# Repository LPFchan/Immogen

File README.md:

# Immogen — Ninebot G30 BLE Immobilizer

**Immogen** is a three-part BLE immobilizer system for the Ninebot Max G30, consisting of **[Uguisu](https://github.com/LPFchan/Immogen/tree/main/Uguisu#readme)** (key fob), **[Guillemot](https://github.com/LPFchan/Immogen/tree/main/Guillemot#readme)** (deck receiver), and **[Whimbrel](https://github.com/LPFchan/Whimbrel)** (Web Serial provisioning app).

Guillemot sits inline between the battery and ESC via an XT60 splice. Without a valid BLE unlock from Uguisu, the scooter stays inoperable. Male/female pigtails keep the install reversible—no permanent modification required.

```
┌─────────────────┐       BLE advertisement        ┌──────────────────────┐
│  UGUISU (FOB)   │ ─────────────────────────────> │ GUILLEMOT (RECEIVER) │
│  XIAO nRF52840  │       (2.4 GHz, ~2 m)          │  XIAO nRF52840       │
└───────┬─────────┘                                └──────────┬───────────┘
        │                                                     │
        │                 ┌────────────────────┐              │
        └──────(USB-C)──> │ WHIMBREL (WEB APP) │ <──(USB-C)───┘
       (Provisioning)     │ Chrome / Edge      │    (Provisioning)
                          └────────────────────┘
```

## Repository Structure

| Path             | Description                                                                                                                                                                       |
| ---------------- | --------------------------------------------------------------------------------------------------------------------------------------------------------------------------------- |
| `Uguisu/`    | Key fob — firmware, KiCad, BOM. Button press → 2 s BLE broadcast → sleep. [README](https://github.com/LPFchan/Immogen/tree/main/Uguisu#readme)                                 |
| `Guillemot/` | Deck receiver — firmware, KiCad, BOM. Duty-cycled scan (5%), validates adverts → SR latch → power gate. [README](https://github.com/LPFchan/Immogen/tree/main/Guillemot#readme) |
| `lib/`       | Shared C++ library: AES-128-CCM MIC, provisioning loop, LittleFS counter storage                                                                                                  |
| `tools/`     | LED visualizer, BLE timing simulator, buzzer tuner (HTML); MIC test vectors (`gen_mic.py`)                                                                                        |
| `logs/`      | Migration reports and guides                                                                                                                                                      |

## BLE Protocol

Advertisement-only; no persistent connection. Both devices share a company ID and pre-shared key (PSK). Each advertisement carries a 13-byte payload after the 2-byte company ID:

| Offset | Size | Field   | Purpose                    |
| ------ | ---- | ------- | -------------------------- |
| 0      | 4    | counter | Anti-replay, monotonic     |
| 4      | 1    | command | 0x01 = Unlock, 0x02 = Lock |
| 5      | 8    | mic     | AES-128-CCM auth tag       |

For full protocol details see the [Guillemot](https://github.com/LPFchan/Immogen/tree/main/Guillemot#readme) and [Uguisu](https://github.com/LPFchan/Immogen/tree/main/Uguisu#readme) READMEs.

## Quick Start

Pre-built firmware is available on the [Releases](https://github.com/LPFchan/Immogen/releases) page. Use [Whimbrel](https://github.com/LPFchan/Whimbrel) to flash and provision keys via Web Serial.

**Build from source:**

```bash
# Deck receiver
cd Guillemot/firmware && pio run

# Key fob
cd Uguisu/firmware && pio run
```

## Roadmap

- Uguisu enclosure CAD (3D print).
- First-build validation: PPK2 power, BLE range through deck, pre-charge waveform.

## Safety & Legal

- Prototype security/power-interrupt device. Use at your own risk.
- Not affiliated with Segway-Ninebot.
- **Do not test lock behavior while riding.**

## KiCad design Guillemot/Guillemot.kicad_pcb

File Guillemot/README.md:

# Guillemot — Ninebot G30 BLE Immobilizer Receiver

Guillemot is the deck receiver in a three-part immobilizer system ([Uguisu](https://github.com/LPFchan/Immogen/tree/main/Uguisu) fob + [Whimbrel](https://github.com/LPFchan/Whimbrel) web app) for the Ninebot Max G30. It validates encrypted BLE advertisements from the fob and controls an SR latch that gates battery-to-ESC power via an inline XT60 splice. Male/female pigtails make it fully reversible—no permanent modification to the vehicle. Protocol and cryptography are handled by the shared [lib/](https://github.com/LPFchan/Immogen/tree/main/lib) in this monorepo ([Immogen](https://github.com/LPFchan/Immogen)).

---

## Hardware

### Placement

Mount Guillemot on the plastic underside of the deck for good 2.4 GHz RF.

### Components & BOM (~$20)

| Ref       | Part            | Notes                                                             | JLCPCB #         | Cost   |
| --------- | --------------- | ----------------------------------------------------------------- | ---------------- | ------ |
| U1        | XIAO nRF52840   | MCU: BLE scanning, latch control, buzzer PWM                      | Seeed            | $8.23  |
| U2        | SN74LVC2G02DCTR | SR latch: Q = unlock. 10 nF + 100 kΩ differentiator for POR pulse | C94600 (ext.)    | $0.53  |
| PS1       | TPSM365R6V3RDNR | Buck: 3–65 V in, 3.3 V/600 mA, 4 μA Iq. Feeds XIAO 3V3 directly.  | C18208843 (ext.) | $3.59  |
| Q1        | IPB042N10N3G    | Main MOSFET: 100 V/137 A, D2PAK, low-side GND return              | C69300 (ext.)    | $0.75  |
| Q2        | AO3422          | Pre-charge FET, inrush ~0.8 A. Driven by latch Q.                 | C37130 (ext.)    | $0.23  |
| Q3        | SI2309CDS       | Bleeder P-FET: disconnects 10 kΩ bleeder when locked (0 μA)       | C10493 (ext.)    | $0.23  |
| Q4        | 2N7002          | Gate drive                                                        | C8545            | $0.01  |
| Q5, Q6    | MMBT3904        | Buzzer driver                                                     | C20526           | $0.02  |
| BZ1       | FUET-1230       | Buzzer: 12×12×3 mm SMD, 4 kHz. Driven by MMBT3904                 | C391037 (ext.)   | $0.47  |
| D1        | BZT52C12-7-F    | 12 V Zener                                                        | C124196 (ext.)   | $0.11  |
| D2        | BZT52C10-7-F    | 10 V Zener                                                        | C155227 (ext.)   | $0.10  |
| D3, D4    | 1N4148W         | Gate isolation from buzzer rail sag                               | C81598           | $0.01  |
| D5        | SMBJ45A         | 45 V TVS diode for transient suppression                          | C114005 (ext.)   | $0.08  |
| C1        | 10 nF (0603)    | POR pulse differentiator                                          | C57112           | $0.003 |
| C2        | 100 µF (1210)   | Bulk decoupling. EMK325ABJ107MM-P 16V X5R ±20%                   | C90143 (ext.)    | $0.31  |
| C3, C4    | 1 µF (0603)     | RC delay bypass, gate isolation                                   | C15849           | $0.01  |
| R1, R2    | 100 kΩ (0603)   | Latch input pull-downs (prevent floating during WDT reset)        | C25803           | $0.006 |
| R3, R7    | 100 kΩ (0603)   | Gate drive, RC delay (τ = 100 ms)                                 | C25803           | $0.006 |
| R4        | 1 MΩ (0603)     | P-FET gate pull-up                                                | C22935           | $0.001 |
| R5        | 10 kΩ (0603)    | Bleeder resistor                                                  | C25804           | $0.001 |
| R6        | 4.7 kΩ (0603)   | Piezo buzzer discharge resistor                                   | C23162           | $0.001 |
| R8        | 47 Ω 2 W (2512) | Pre-charge resistor, inrush ~0.77–0.89 A                         | C136992 (ext.)   | $0.10  |
| TP1–5     | XT60 + 12 AWG   | Pigtails and GND jumper                                           | Generic          | —      |
| —         | PCB             | 54×34 mm, 2 oz outer                                              | JLCPCB           | $1.60  |

JLCPCB P&P for SMT. Hand-solder XIAO edges, XT60 pigtails, and the GND jumper.

### PCB Layout

4-layer, 54×34 mm, 2 oz outer copper, designed for 30 A continuous.

- **12 AWG GND jumper (critical):** Main battery return bypasses inner layers. Run an external silicone wire from the `BAT-` XT60 pad to the MOSFET source pad.
- **Power traces:** `+BATT` and `ESC-` as top-layer pours. No high-current vias.
- **Clearance:** ≥ 0.6 mm between 42 V power and 3.3 V logic.
- **Pre-charge trace:** Q2 → R8 → `ESC-` routed at **1.0 mm** to survive initial ~40 W inrush surge.
- **RF keepout:** Strip copper on all layers under the XIAO's BLE antenna trace.
- **Assembly:** Single-sided (F.Cu) SMT for easy JLCPCB PCBA.

### Operation

- **Unlock flow:** Uguisu advert → MCU validates → SET latch → Q HIGH → pre-charge 100 ms → MOSFET ON → buzzer tone.
- **Lock flow:** Uguisu advert → MCU validates → buzzer tone → RESET latch → Q LOW → P-FET OFF, pre-charge OFF → MOSFET OFF.
- **Power (locked):** ~306 μA (buck Iq + 5% duty-cycled scan + latch). At 306 μA, a G30 (15.3 Ah) would theoretically take ~5.7 years to drain; battery self-discharge (~12 months) dominates in practice. See `logs/15-BLE_POWER_ANALYSIS_AND_DOCUMENTATION_DISCREPANCY.md` for derivation.
- **Buzzer timing:** Unlock tone ~34 ms after 10 V rail up; lock tone before RESET.

### Design Notes

- **EasyEDA → KiCad:** Schematics and PCBs are designed in KiCad. [easyeda2kicad](https://github.com/wokwi/easyeda2kicad) is used to import symbols and footprints from EasyEDA/LCSC. Example: `easyeda2kicad --full --lcsc_id=Cxxxx` (replace `Cxxxx` with the LCSC part number).
- **Latch Input Pull-downs (100 kΩ):** R1 and R2 hold `MCU_D0` (SET) and `MCU_D1` (RESET) strictly LOW. This is critical because the nRF52840's pins float (high-impedance) during the 8-second hardware Watchdog Timer (WDT) reset cycle. Without these resistors, noise or capacitive coupling could randomly toggle the latch and power state while the MCU reboots.
- **AO3422:** 55 V Vds provides margin over the 42 V bus when locked.
- **Gate drive R (100 kΩ):** Protects the 2N7002 and BZT Zeners.
- **POR circuit (10 nF + 100 kΩ):** 1 ms RC differentiator—brief pulse zeros the latch at power-on.
- **RC delay (100 kΩ + 1 μF):** 1N4148W bypass for fast turn-off.
- **Gate isolation (1N4148W + cap):** Buzzer draw exceeds bleeder supply; diode and 1 μF hold cap prevent gate sag during tones (Vgs ≈ 9.3 V).
- **Gate pull-down (MMBT3904):** Via Q̄/RC, discharges hold cap for instant OFF.
- **IPB042N10N3G:** Outperforms TO-220 standing upright in sealed deck enclosures when thermal pad is stitched to B.Cu. **IPB035N10NF2S (3.5 mΩ)** is the long-term successor depending on LCSC stock.

---

## Software

### Firmware

[PlatformIO](https://platformio.org/) project in `firmware/`

Scanning is duty-cycled (25 ms every 500 ms, 5% duty) for reliable detection. P(detect) = 100% per button press because `scanWindow (25 ms) ≥ advInterval (20 ms)` guarantees full phase coverage. The receiver rejects any payload with an invalid AES-CCM MIC or a counter less than or equal to the last seen value (anti-replay). The receiver is also protected against MCU hangs by an 8-second hardware Watchdog Timer (WDT) which triggers a clean reboot without disrupting the latch state.

### Protocol

Validation and crypto via shared [lib/](https://github.com/LPFchan/Immogen/tree/main/lib). See [Immogen README § BLE Protocol](https://github.com/LPFchan/Immogen#ble-protocol) for full specification.

### Onboarding

Use [Whimbrel](https://github.com/LPFchan/Whimbrel) for both tasks:

- **Firmware flashing:** Web-based flasher via Web Serial. Enter bootloader mode with a double-tap on reset.
- **Key provisioning:** Connect via USB; Whimbrel injects the shared AES-128 key. Physical presence is required. The firmware has no serial commands to read the key back.

---

## Safety & Notes

- Prototype security and power-interrupt device. Use at your own risk.
- Do not test lock behavior while riding.
- Not affiliated with Segway-Ninebot.
- Avoid committing KiCad per-user state (`*.kicad_prl`) or lock files.

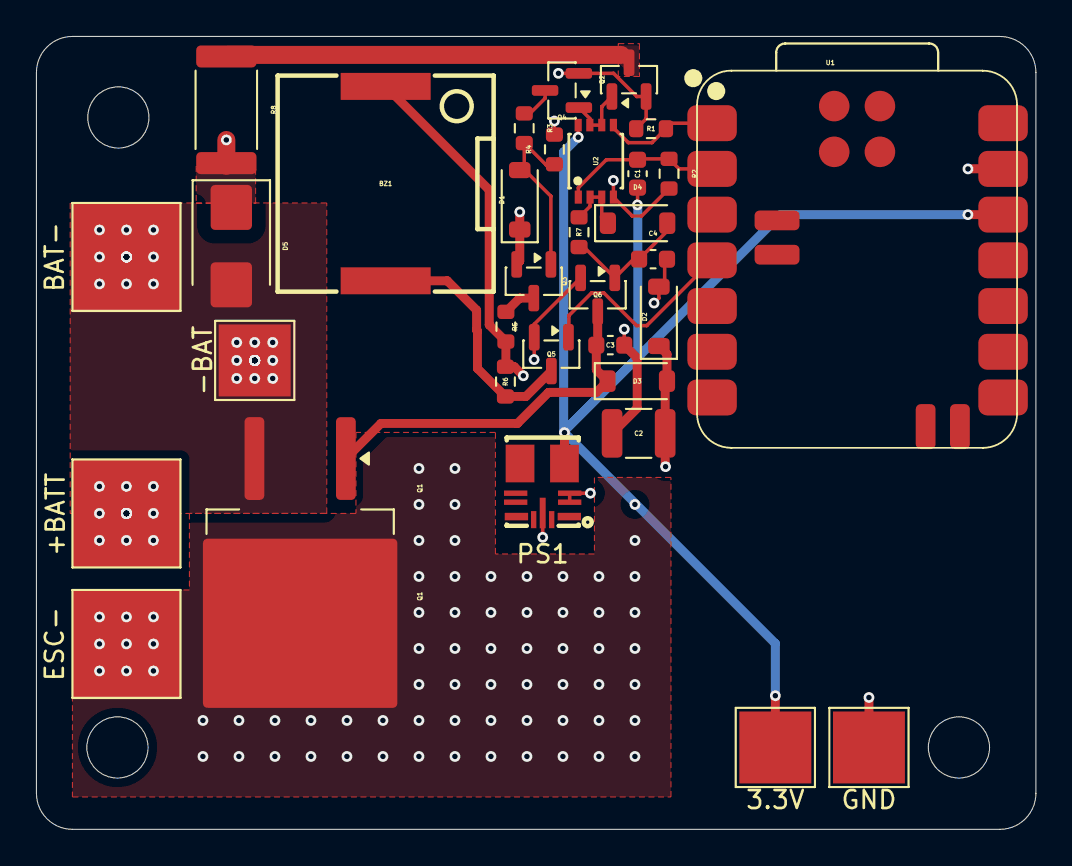
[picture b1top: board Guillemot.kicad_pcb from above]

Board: 4 copper layers, 55.5 x 44.0 mm, 33 parts (0 on the bottom side), 17 nets.

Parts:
3.3V: 3.3V; TestPoint_Pad_4.0x4.0mm
+BATT: ESC+; TestPoint_Pad_6.0x6.0mm
-BAT: WIRE; TestPoint_Pad_4.0x4.0mm
BAT-: BAT-; TestPoint_Pad_6.0x6.0mm
BZ1: FUET-1230; BUZ-SMD_L12.0-W12.0_FUET-1230
C1: 10nF; C_0603_1608Metric
C2: 100µF; C_1210_3225Metric
C3, C4: 1uF; C_0603_1608Metric
D1: BZT52C12-7-F; D_SOD-123
D2: BZT52C10-7-F; D_SOD-123
D3, D4: 1N4148W; D_SOD-123
D5: SMBJ45A; D_SMB
ESC-: ESC-; TestPoint_Pad_6.0x6.0mm
GND: GND; TestPoint_Pad_4.0x4.0mm
PS1: TPSM365R6V3RDNR; QFN-11_L4.5-W3.5-P0.50-TL_TPSM365R6FRDNR
Q1: IPB042N10N3G; TO-263-2
Q2: AO3422; SOT-23
Q3: SI2309CDS; SOT-23
Q4: 2N7002; SOT-23
Q5, Q6: MMBT3904; SOT-23
R1, R2, R3, R7: 100k; R_0603_1608Metric
R4: 1M; R_0603_1608Metric
R5: 10k; R_0603_1608Metric
R6: 4.7k; R_0603_1608Metric
R8: 47 2W; R_2512_6332Metric
U1: XIAO-nRF52840-SMD
U2: SN74LVC2G02DCTR; MSOP-8_L2.9-W2.8-P0.65-LS4.0-BR

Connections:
+BATT: +BATT.1, D1.1 (K), PS1.2 (EN), PS1.3 (VIN), Q3.2 (S), R4.2
/3.3V: 3.3V.1, C1.2, PS1.4 (VOUT), U1.12 (3V3), U2.8 (VCC)
/10V_RAIL: BZ1.1 (+), C2.1, D2.1 (K), D3.2 (A), R5.2, R6.1
/10V_RAW: Q3.3 (D), R5.1
/BUZZER_SINK: BZ1.2, Q5.3 (C), R6.2
/ESC-: D5.1 (A1), ESC-.1, Q1.2 (D), R8.2
/ISO_GATE: C3.1, D3.1 (K), Q1.1 (G), Q6.3 (C)
/MCU_D0: R1.1, U1.1 (P0.02_A0_D0), U2.5 (2A)
/MCU_D1: C1.1, R2.1, U1.2 (P0.03_A1_D1), U2.1 (1A)
/MCU_D3: Q5.1 (B), U1.4 (P0.29_A3_D3)
/NPN_BASE: C4.1, D4.2 (A), Q6.1 (B), R7.2
/PFET_CTRL: Q4.3 (D), R3.1
/PFET_GATE: D1.2 (A), Q3.1 (G), R3.2, R4.1
/PRECHARGE_OUT: Q2.3 (D), R8.1
/QBAR_LOCK: D4.1 (K), R7.1, U2.2 (1B), U2.3 (2Y)
/Q_UNLOCK: Q2.1 (G), Q4.1 (G), U2.6 (2B), U2.7 (1Y)
GND: -BAT.1, BAT-.1, C2.2, C3.2, C4.2, D2.2 (A), D5.2 (A2), GND.1, PS1.10 (GND), Q1.3 (S), Q2.2 (S), Q4.2 (S), Q5.2 (E), Q6.2 (E), R1.2, R2.2, U1.13 (GND), U2.4 (GND)

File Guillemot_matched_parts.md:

# Guillemot BOM - Matched Parts

## Matched Components


| Designator  | Comment         | Footprint                       | Part Name               | LCSC      | Description / Specs                                                                                                                | Qty | Type     | Total Cost |
| ----------- | --------------- | ------------------------------- | ----------------------- | --------- | ---------------------------------------------------------------------------------------------------------------------------------- | --- | -------- | ---------- |
| BZ1         | FUET-1230       | BUZ-SMD_L12.0-W12.0_FUET-1230   | FUET-1230               | C391037   | -20℃~~+70℃ 12mm 12mm 1V~~25V 3.3mm 3V 4kHz 5mA 75dB Passive (Externally Driven) Piezoelectric SMD,12x12mm Buzzers ROHS             | 5   | Extended | $2.3640    |
| C1          | 10nF            | 0603                            | 0603B103K500NT          | C57112    | 10nF 50V X7R ±10% 0603 Multilayer Ceramic Capacitors MLCC - SMD/SMT ROHS                                                           | 5   | Basic    | $0.0140    |
| C2          | 100µF           | 1210                            | CL32A107MPVNNNE         | C23742    | 100uF 10V X5R ±20% 1210 Multilayer Ceramic Capacitors MLCC - SMD/SMT ROHS                                                          | 5   | Extended | $1.5285    |
| C3,C4       | 1uF             | 0603                            | CL10A105KB8NNNC         | C15849    | 1uF 50V X5R ±10% 0603 Multilayer Ceramic Capacitors MLCC - SMD/SMT ROHS                                                            | 5   | Basic    | $0.0720    |
| D1          | BZT52C12-7-F    | D_SOD-123                       | BZT52C12-7-F            | C124196   | -65℃~~+150℃ 100nA@1V 11.4V~~12.7V 12V 150Ω 25Ω 370mW Independent SOD-123 Zener Diodes ROHS                                         | 5   | Extended | $0.5538    |
| D2          | BZT52C10-7-F    | D_SOD-123                       | BZT52C10-7-F            | C155227   | -65℃~~+150℃ 10V 150Ω 200nA 20Ω 370mW 9.4V~~10.6V Independent SOD-123 Zener Diodes ROHS                                             | 5   | Extended | $0.5085    |
| D3,D4       | 1N4148W         | D_SOD-123                       | 1N4148W                 | C81598    | 1.25V@150mA 100V 150mA 1uA@75V 2A 4ns 500mW Independent SOD-123 Switching Diodes ROHS                                              | 10  | Basic    | $0.1100    |
| D5          | SMBJ45A         | D_SMB                           | SMBJ45A                 | C114005   | -65℃~+150℃ 1uA 45V 55.3V 600W@10/1000us 72.7V 8.3A@10/1000us TVS Unidirectional DO-214AA(SMB) ESD and Surge Protection             | 5   | Extended | $0.4221    |
| PS1         | TPSM365R6V3RDNR | CONV_TPSM365R6V3RDNR            | TPSM365R6V3RDNR         | C18208843 | -40℃~~+125℃ 1MHz 2mm 3.3V 3.5mm 3.6V~~65V 4.5mm 4uA 600mA 80.2% Buck Overheat protection、Over Current Protection ±1.5%             | 5   | Extended | $17.9375   |
| Q1          | IPB042N10N3G    | TO-263-2                        | IPB042N10N3G            | C69300    | -55℃~+175℃ 1 N-channel 100V 117nC 137A 214W 3.5V 4.2mΩ@10V 41pF 8.41nF TO-263-3 MOSFETs ROHS                                       | 5   | Extended | $3.7630    |
| Q2          | AO3422          | SOT-23                          | AO3422                  | C37130    | 1 N-channel 10A 12.6pF 160mΩ@4.5V 2V [3.3nC@4.5V](mailto:3.3nC@4.5V) 300pF 55V N-Channel SOT-23 MOSFETs ROHS                       | 5   | Extended | $1.1376    |
| Q3          | SI2309CDS       | SOT-23                          | SI2309CDS-T1-GE3        | C10493    | -55℃~+150℃ 1 P-Channel 1.6A 1.7W 20pF 210pF 28pF 3V [4.1nC@4.5V](mailto:4.1nC@4.5V) 450mΩ@4.5V 60V P-Channel SOT-23-3 MOSFETs ROHS | 5   | Extended | $1.1333    |
| Q4          | 2N7002          | SOT-23                          | 2N7002                  | C8545     | 1 N-channel 115mA 2.5V 225mW 50pF 5pF 5Ω@10V 60V SOT-23 MOSFETs ROHS                                                               | 5   | Basic    | $0.0660    |
| Q5,Q6       | MMBT3904        | SOT-23                          | MMBT3904(RANGE:100-300) | C20526    | -55℃~+150℃ 1 NPN 100 100nA 200mA 200mW 300MHz 300mV 40V 6V NPN SOT-23 Bipolar (BJT) ROHS                                           | 5   | Basic    | $0.0950    |
| R1,R2,R3,R7 | 100k            | 0603                            | 0603WAF1003T5E          | C25803    | -55℃~+155℃ 100kΩ 100mW 75V Thick Film Resistor ±1% ±100ppm/℃ 0603 Chip Resistor - Surface Mount ROHS                               | 5   | Basic    | $0.0280    |
| R4          | 1M              | 0603                            | 0603WAF1004T5E          | C22935    | -55℃~+155℃ 100mW 1MΩ 75V Thick Film Resistor ±1% ±100ppm/℃ 0603 Chip Resistor - Surface Mount ROHS                                 | 5   | Basic    | $0.0065    |
| R5          | 10k             | 0603                            | 0603WAF1002T5E          | C25804    | -55℃~+155℃ 100mW 10kΩ 75V Thick Film Resistor ±1% ±100ppm/℃ 0603 Chip Resistor - Surface Mount ROHS                                | 5   | Basic    | $0.0065    |
| R6          | 4.7k            | 0603                            | 0603WAF4701T5E          | C23162    | -55℃~+155℃ 100mW 4.7kΩ 75V Thick Film Resistor ±1% ±100ppm/℃ 0603 Chip Resistor - Surface Mount ROHS                               | 5   | Basic    | $0.0065    |
| R8          | 472W            | 2512                            | RC2512JK-7W47RL         | C136992   | -55℃~+155℃ 200V 2W 47Ω Thick Film Resistor ±200ppm/℃ ±5% 2512 Chip Resistor - Surface Mount ROHS                                   | 5   | Extended | $0.5184    |
| U2          | SN74LVC2G02DCTR | MSOP-8_L2.9-W2.8-P0.65-LS4.0-BR | SN74LVC2G02DCTR         | C94600    | -40℃~~+125℃ 1.2V、1.9V、2.3V、2.4V、3.8V 1.65V~~5.5V 1.7V~2V 10uA 2 2 300mV、400mV、450mV、550mV 32mA 32mA 4.4ns@5V,50pF 74LVC            | 5   | Extended | $2.6565    |


## Unmatched Components


| Designator | Comment           |
| ---------- | ----------------- |
| U1         | XIAO-nRF52840-SMD |

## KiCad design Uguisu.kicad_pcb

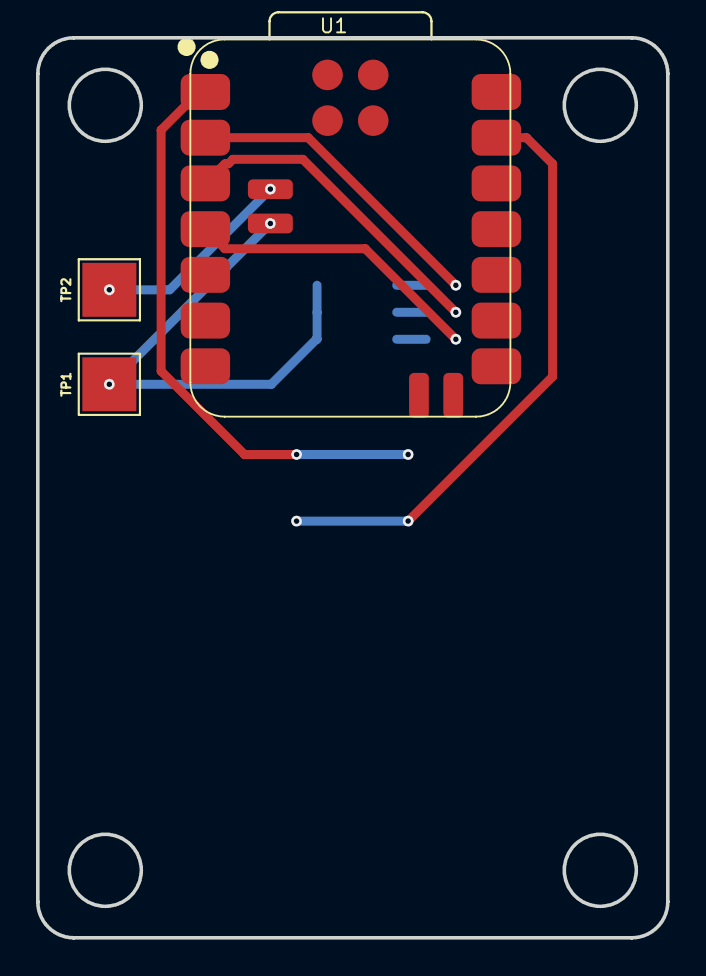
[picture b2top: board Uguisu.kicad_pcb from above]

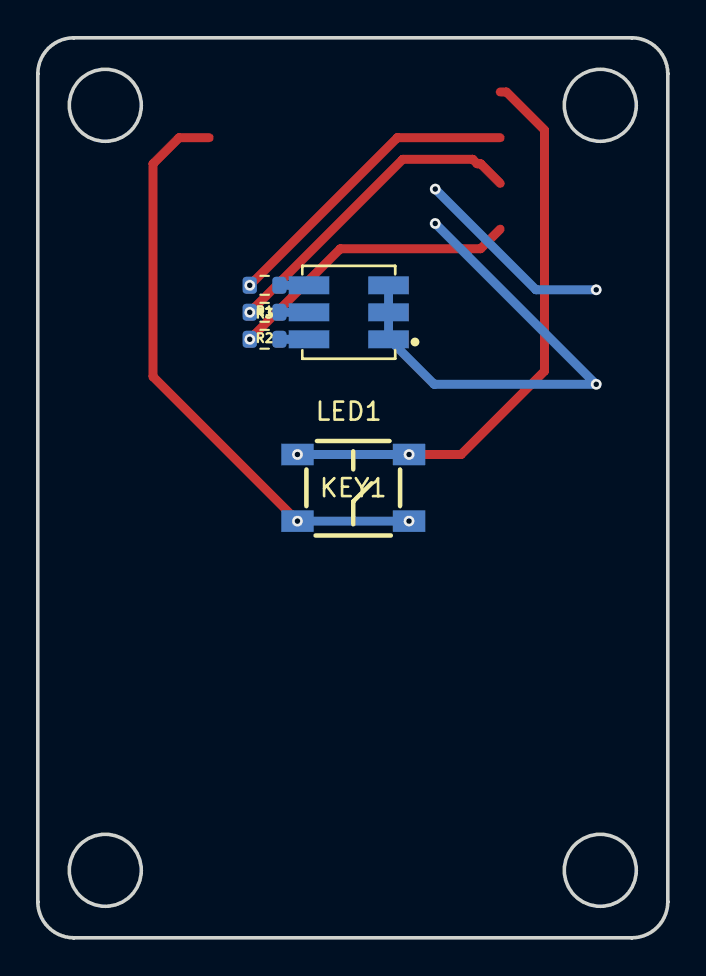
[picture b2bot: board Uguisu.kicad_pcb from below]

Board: 2 copper layers, 35.0 x 50.0 mm, 8 parts (5 on the bottom side), 9 nets.

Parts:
KEY1: SKQGABE010; KEY-SMD_4P-L5.2-W5.2-P3.70-LS6.4
LED1: TC5050RGBF08-3CJH-AF53A; LED-SMD_6P-L5.0-W5.0-TL_TC5050RGBF08
R1: 120; R_0603_1608Metric
R2: 330; R_0603_1608Metric
R3: 150; R_0603_1608Metric
TP1: +BATT; TestPoint_Pad_3.0x3.0mm
TP2: GND; TestPoint_Pad_3.0x3.0mm
U1: XIAO-nRF52840-SMD

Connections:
+BATT: LED1.1 (+), LED1.2 (+), LED1.3 (+), TP1.1, U1.32 (BAT)
/MCU_D0: KEY1.1, KEY1.2, U1.1 (P0.02_A0_D0)
/MCU_D1: R1.2, U1.2 (P0.03_A1_D1)
/MCU_D2: R2.2, U1.3 (P0.28_A2_D2)
/MCU_D3: R3.1, U1.4 (P0.29_A3_D3)
GND: KEY1.3, KEY1.4, TP2.1, U1.13 (GND), U1.33 (GND)
unnamed: LED1.4 (-), R1.1
unnamed: LED1.5 (-), R2.1
unnamed: LED1.6 (-), R3.2

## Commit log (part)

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2026-03-06 Initial Guillemot hardware + receiver firmware
    Add KiCad design files and production outputs, plus a PlatformIO-based nRF52840 receiver firmware that duty-cycles BLE scanning, verifies AES-CCM MIC + anti-replay counter, and drives latch/buzzer GP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
    Made-with: Cursor
2026-03-06 Add Uguisu firmware skeleton and MIC test vectors
    Introduce a PlatformIO/Arduino firmware scaffold that generates AES-CCM MICs compatible with Guillemot, plus Python test vectors and documentation.
2026-03-06 Whimbrel compatibility: VBUS provisioning, PROV: serial protocol, runtime key/device_id from flash
    Made-with: Cursor
2026-03-06 Fix release: disable generate_release_notes (GITHUB_TOKEN 403)
    Made-with: Cursor
2026-03-06 Release workflow: grant contents: write so GITHUB_TOKEN can create releases
    Made-with: Cursor
2026-03-06 Release: use RELEASE_TOKEN secret (PAT); add RELEASE-SETUP.md
    Made-with: Cursor
2026-03-06 refactor: extract common modules and update documentation
    - Extracted duplicated crypto, provisioning, and storage logic into a shared `lib/ImmoCommon` module
    - Refactored `main.cpp` to use the new shared modules
    - Removed old `uguisu_protocol.cpp` and `uguisu_protocol.h` files
    - Updated `README.md` to use the unified structure and tone
    - Added explanatory comments to `platformio.ini` regarding `extra_scripts.py`
    Made-with: Cursor
2026-03-06 Initial commit: Extract ImmoCommon library
    Made-with: Cursor
2026-03-06 chore: replace ImmoCommon folder with git submodule
    Made-with: Cursor
2026-03-06 ci: fetch submodules on release
    Made-with: Cursor
2026-03-06 Refactor: Use ImmoCommon and ensure_provisioned() helper
    Made-with: Cursor
2026-03-06 Docs: Cross-link related repositories
    Made-with: Cursor
2026-03-06 Update ImmoCommon submodule
    Made-with: Cursor
2026-03-06 Docs: Standardize format and remove bloat
    Made-with: Cursor
2026-03-06 Docs: Enrich README with hardware/power details
    Made-with: Cursor
2026-03-06 CI: Fix GitHub Actions permissions to allow creating releases
    Made-with: Cursor
2026-03-06 docs: update README with firmware flashing capability
    Updates the documentation to clarify that Whimbrel is now used for both key provisioning and flashing firmware updates via Web Serial.
    Made-with: Cursor
2026-03-06 Add shared gen_mic.py test vectors, update README
    Made-with: Cursor
2026-03-06 LED error loop, migrate gen_mic to ImmoCommon, update ImmoCommon submodule
    - Add LED blink error loop when InternalFS.begin() fails
    - Add PIN_ERROR_LED to config (default: XIAO red LED)
    - Migrate gen_mic.py to ImmoCommon submodule
    - Update PROTOCOL.md and tools/test_vectors/README.md
    Made-with: Cursor
2026-03-06 Single press = unlock, long press = lock; migrate gen_mic to ImmoCommon
    - Add button handling: short press = Unlock, long press (2s) = Lock
    - Add UGUISU_LONG_PRESS_MS config, wait_for_button_press_release()
    - Migrate gen_mic.py to ImmoCommon submodule
    - Update tools/test_vectors/README.md
    Made-with: Cursor
2026-03-06 Drop device_id: 9-byte payload, single counter, PROV:key:counter:checksum
    - Parse 9-byte MSD (counter, command, mic)
    - verify_payload / handle_valid_command use lastCounter(), update(counter)
    - on_provision_success(key, counter), seed receiver on provision
    - Update ImmoCommon submodule
    Made-with: Cursor
2026-03-06 Drop device_id: 9-byte payload, prov file key-only, PROV:key:counter:checksum
    - Remove UGUISU_DEVICE_ID and g_device_id
    - Prov file: magic+key (20 bytes) only
    - Build 9-byte payload with build_nonce(counter), build_msg(counter, command)
    - Update ImmoCommon submodule
    Made-with: Cursor
2026-03-06 Update ImmoCommon submodule; align lock long-press comment to 1s
    Made-with: Cursor
2026-03-07 Replace README with combined design doc content
    Made-with: Cursor
2026-03-07 Add NVS wear note to storage section
    Made-with: Cursor
2026-03-07 Unify company ID to MSD_COMPANY_ID, update protocol spec link
    Made-with: Cursor
2026-03-07 Format README table
    Made-with: Cursor
2026-03-07 Update README BOM ref numbers to match production BOM
    Made-with: Cursor
2026-03-07 README: GPIO table with LED1 pin 4,5,6 in notes
    Made-with: Cursor
2026-03-07 Update PCB layout
    Made-with: Cursor
2026-03-07 README and PCB updates
    Made-with: Cursor
2026-03-07 Ignore production artifacts in git
    Added the production folder to .gitignore.
    Made-with: Cursor
2026-03-07 docs: sort BOM sensibly (ICs, power, discrete, passives)
    Made-with: Cursor
2026-03-07 docs: annotate extended parts in BOM
    Made-with: Cursor
2026-03-07 Add BOM matched parts doc, update README
    Made-with: Cursor
2026-03-07 Stop tracking production folder; add production/ to .gitignore
    Made-with: Cursor
2026-03-08 Remove fix_readme_cost.py, stop tracking production folder (in .gitignore)
    Made-with: Cursor
2026-03-08 build: add shared immo_tusb_config.h to disable MSC and prevent File class collision
    Made-with: Cursor
2026-03-08 build: consume shared immo_tusb_config.h from ImmoCommon
    Made-with: Cursor
2026-03-08 Move docs into docs/ folder
    Made-with: Cursor
2026-03-08 docs: move architecture, critique, matched parts, review response, MIC proposal into logs/
    Made-with: Cursor
2026-03-08 Upgrade AES-CCM MIC from 4 to 8 bytes
    - MIC_LEN 4->8, PAYLOAD_LEN 9->13
    - Rename ccm_mic_4 to ccm_mic_8
    - Update gen_mic.py for 8-byte tag
    - Update documentation
    Made-with: Cursor
2026-03-08 8-byte MIC upgrade: update ImmoCommon submodule, use ccm_mic_8
    Made-with: Cursor
2026-03-08 Rename docs/ to logs/
    Made-with: Cursor
2026-03-09 refactor: unify PSK storage, add utils, fix counter and dead code
    - prov_write_and_verify() + prov_load_key() in immo_provisioning: normalized
    PSK flash format (PROV_MAGIC 0x564F5250 + key) shared by both devices,
    eliminating per-device on_provision_success boilerplate
    - New immo_util module: is_key_blank() and led_error_loop(pin) extracted from
    duplicate copies in guillemot/main.cpp and uguisu/main.cpp
    - immo_storage: CounterStore::load() now tracks max counter seen, not last,
2026-03-09 refactor: use ImmoCommon prov/util helpers, normalize PSK storage path
    - on_provision_success: delegate to immo::prov_write_and_verify() — formats
    PSK as PROV_MAGIC + key (20B), removes redundant InternalFS.remove calls
    - load_psk_from_storage: delegate to immo::prov_load_key()
    - PSK storage path changed from /psk.bin to /prov.bin (re-provisioning required)
    - key_is_all_zeros: thin wrapper over immo::is_key_blank()
    - led_error_loop: replaced with immo::led_error_loop(PIN_ERROR_LED)
2026-03-09 Remove unused GUILLEMOT_BUILD_PIO build flag from platformio.ini
2026-03-09 feat: implement LED feedback, battery check, and provisioning task
    - Add readVbat_mv() to uguisu_config.example.h (P0.31/AIN7, 1MΩ/1MΩ
    divider, AR_INTERNAL_3_0, 12-bit: raw * 6000 / 4096)
    - Add prov_led_task (FreeRTOS) for blue pulse during serial provisioning;
    started only when VBUS is present, deleted after ensure_provisioned()
    - Determine cmd_pin and low_bat after button press; branch to
    flash_low_battery(cmd_pin) or flash_once(cmd_pin) accordingly
2026-03-09 hw: add 3.3V and GND test point pads for AirTag power tap
    - Label U1 3V3 pin as /3.3V net (was unconnected)
    - Add 3x3mm SMD test point pads for 3.3V and GND adjacent to XIAO
    - Rename existing BATT/GND test points with clearer silkscreen labels
    - Route 3.3V net to test point via back copper
2026-03-09 refactor: rename config header to guillemot_nrf52840.h, two-tone buzzer, add buzzer tuner
    - Rename guillemot_config.example.h → guillemot_nrf52840.h to match Uguisu
    naming convention (board-specific defaults clearly identified)
    - Add __has_include("guillemot_config_local.h") override guard to guillemot_config.h
    - Move latch_set_pulse() and latch_reset_pulse() from main.cpp into
    guillemot_nrf52840.h as inline board-specific hardware functions
    - Replace single BUZZER_HZ/UNLOCK_MS/LOCK_MS with two-tone defines:
2026-03-09 Add REVIEW_RESPONSE_KO.md
    Made-with: Cursor
2026-03-09 tune: set BLE timing to 500/20 ms scan, 600/20 ms advertise
    Guillemot: SCAN_INTERVAL_MS 2000→500, SCAN_WINDOW_MS 20→20 (no change).
    Uguisu: UGUISU_ADVERTISE_MS 2000→600, UGUISU_ADV_INTERVAL_MS 100→20.
    20 ms is the minimum legacy advertising interval on S140 SoftDevice.
    Also adds ble_timing_simulator.html with updated defaults matching firmware.
2026-03-09 Stop provisioning timeout once PROV data starts arriving
    Made-with: Cursor
2026-03-09 Restructure: move src and tools into lib/ for monorepo layout
    Made-with: Cursor
2026-03-09 Integrate Guillemot: flatten firmware, remove lib submodule, point to in-tree lib
    Made-with: Cursor
2026-03-09 Integrate Uguisu: flatten firmware, remove submodule, consolidate tools to /tools
    Made-with: Cursor
2026-03-09 Single release workflow: build both firmwares, four artifacts per tag
    Made-with: Cursor
2026-03-09 Flatten lib/src to lib/
    Made-with: Cursor
2026-03-09 Fix firmware builds: add lib as PlatformIO symlink dependency, library.json
    Made-with: Cursor
2026-03-09 lib: bump version to 0.1.0, update description for Immogen
    Made-with: Cursor
2026-03-09 Add project logs to monorepo
    Made-with: Cursor
2026-03-09 Add .gitignore with .DS_Store
    Made-with: Cursor
2026-03-09 feat(simulator): link-intervals toggle + phase slider sync on press
    - Add toggle to lock scan interval ↔ adv duration and scan window ↔
    packet interval; bidirectional, clamped to each slider's range
    - Sync phase offset slider position to the random phase used on
    'Press Fob Button' so the strip highlight matches the timeline
2026-03-09 docs: Uguisu README updates, BLE power analysis, log cleanup
    - Uguisu README: updates (duty cycle, power refs)
    - Add logs/15-BLE_POWER_ANALYSIS_AND_DOCUMENTATION_DISCREPANCY.md
    - Remove logs: BLE_SCAN_DUTY_CYCLE, FULL_CODEBASE_DOCUMENTATION,
    REVIEW_FIXES_TECHNICAL_WRITEUP
    - Add logs/ai_studio_code(13).html
    Made-with: Cursor
2026-03-09 Update README
    Made-with: Cursor
2026-03-09 Rename logs with zero-padded numbering
    Made-with: Cursor
2026-03-09 Reorganize: move KiCad to hardware/, remove tools, consolidate .gitignore
    - Move KiCad files to Guillemot/hardware/ and Uguisu/hardware/
    - Remove Guillemot/tools and Uguisu/tools
    - Merge all .gitignore rules into root .gitignore
    Made-with: Cursor
2026-03-10 docs: standardize log date format, document latch pull-downs, add MCU reset analysis
    - Guillemot README: BOM split for R1/R2 latch pull-downs, design note on WDT reset safety
    - logs: standardize all to *Date: YYYY-MM-DD HH:mm*
    - Add logs/26-MCU_RESET_LATCH_STABILITY.md
    Made-with: Cursor
2026-03-10 docs: finalize Pipit BLE comms, passkey security, and stateful beaconing
2026-03-11 docs(pipit): update master architecture with dynamic beaconing and edge case handling
2026-03-11 docs(pipit): resolve recovery deadlock, mitigate BLE DoS, and normalize terminology
2026-03-11 feat(firmware): Update Guillemot and Uguisu for Pipit app integration
2026-03-11 feat: implement Pipit architecture (4-slot keys, dual BLE roles, SMP)
